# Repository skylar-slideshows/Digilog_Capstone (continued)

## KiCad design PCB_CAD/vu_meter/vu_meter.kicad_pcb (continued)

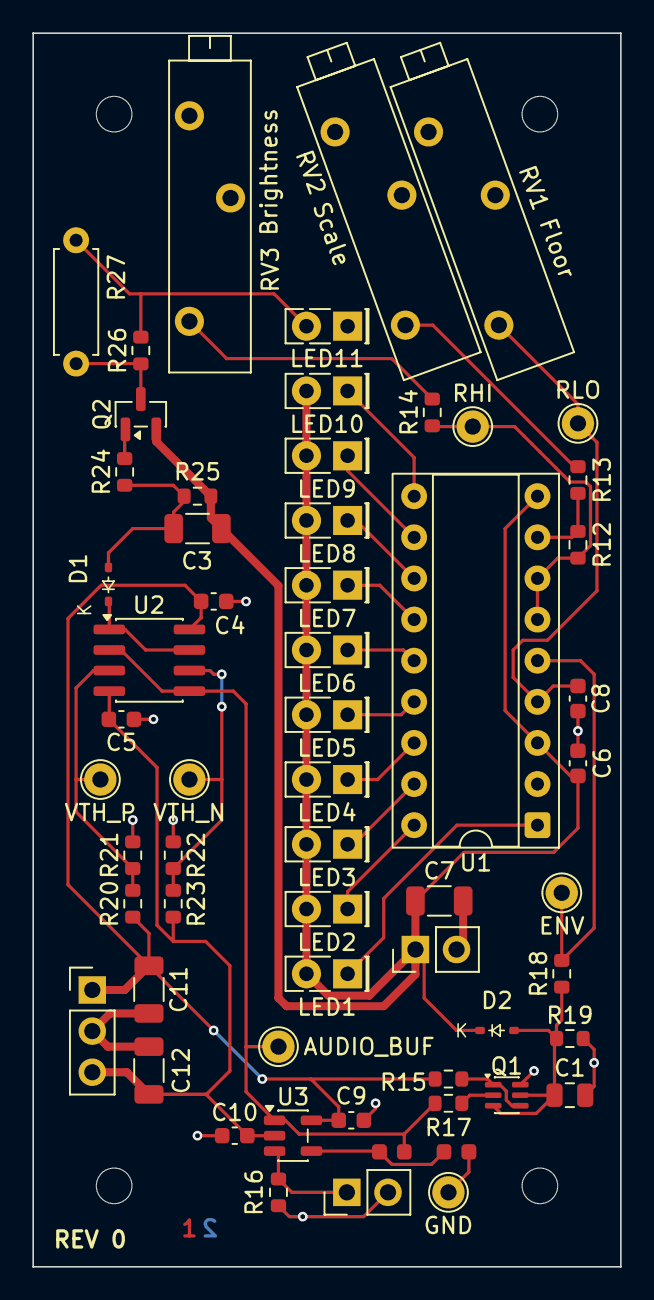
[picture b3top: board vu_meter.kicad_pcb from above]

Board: 2 copper layers, 36.3 x 76.2 mm, 64 parts (0 on the bottom side), 33 nets.

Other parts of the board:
H1, H2, H3, H4: MountingHole_2.2mm_M2

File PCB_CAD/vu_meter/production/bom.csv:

Designator,Footprint,Quantity,Value,LCSC Part #
C1,0805,1,1u,C28323
"C10, C4, C5, C6, C8, C9",0603,6,100n,C1591
"C11, C12, C7",1206,3,10u,C13585
C3,1206,1,2.2u,C50254
D1,D_SOD-323,1,1N4148,C2128
D2,D_SOD-323,1,1N4148WS,C2128
J1,PinHeader_1x03_P2.54mm_Vertical,1,+15 / GND / -15,DNP
J2,PinHeader_1x02_P2.54mm_Vertical,1,+5 / GND,DNP
J3,PinHeader_1x02_P2.54mm_Vertical,1,AUDIO_IN / GND,DNP
"LED1, LED2, LED3, LED4, LED5, LED6, LED7",LED_Rectangular_W5.0mm_H2.0mm,7,LED green,DNP
"LED10, LED8, LED9",LED_Rectangular_W5.0mm_H2.0mm,3,LED yellow,DNP
LED11,LED_Rectangular_W5.0mm_H2.0mm,1,PEAK red,DNP
Q1,SOT-363_SC-70-6,1,MMDT3906,C508227
Q2,SOT-23,1,MMBT3906,C82762
R12,0603,1,3.6k,C22980
R13,0603,1,2.2k,C4190
R14,0603,1,1.5k,C22843
R15,0603,1,15k,C22809
"R16, R25",0603,2,100k,C25803
R17,0603,1,1k,C21190
"R18, R28, R29",0603,3,10k,C25804
R19,0603,1,680k,C25822
"R20, R23",0603,2,330k,C23137
"R21, R22",0603,2,220k,C22961
R24,0603,1,150k,C22807
R26,0603,1,330,C23138
"RV1, RV2",Potentiometer_Bourns_3006P_Horizontal,2,2k,DNP
RV3,Potentiometer_Bourns_3006P_Horizontal,1,10k,DNP
U1,DIP-18_W7.62mm_Socket,1,LM3916,DNP
U2,SOIC-8_3.9x4.9mm_P1.27mm,1,LM393B,C2865059
U3,SOT-23-5,1,TL071H,C4370629

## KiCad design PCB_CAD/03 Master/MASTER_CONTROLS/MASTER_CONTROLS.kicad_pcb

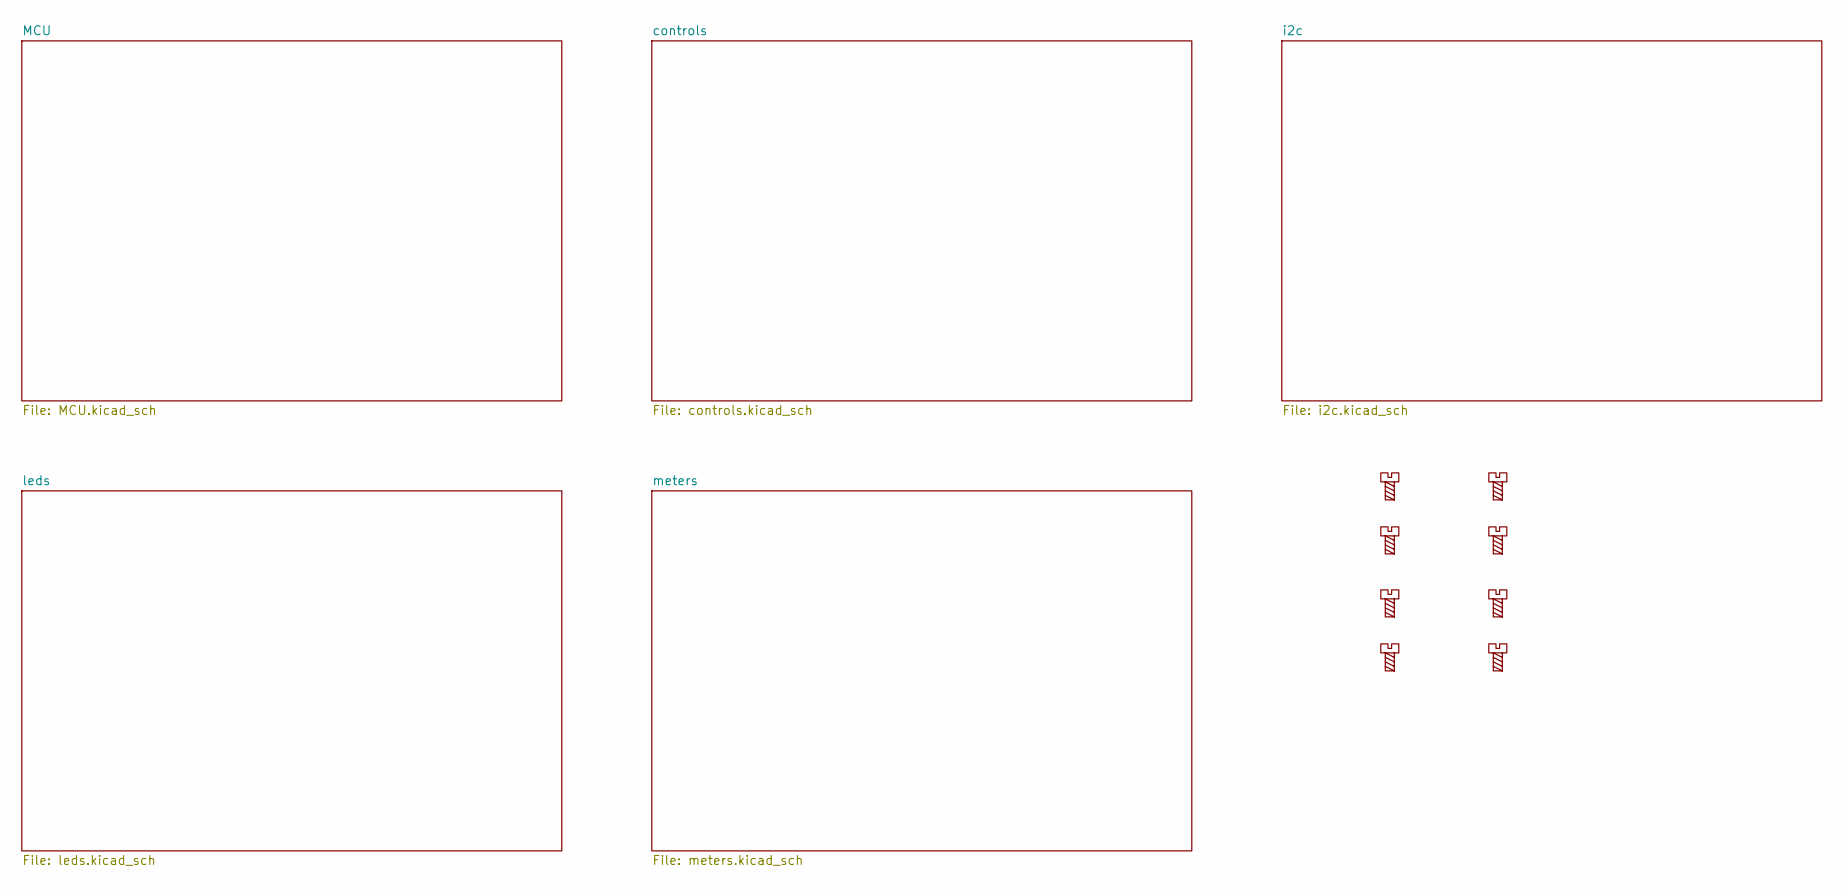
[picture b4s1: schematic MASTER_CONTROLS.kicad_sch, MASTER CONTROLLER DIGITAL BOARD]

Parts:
H1, H2, H3, H4, H5, H6, H7, H8: MountingScrew; MountingHole_3.2mm_M3; LCSC dnp

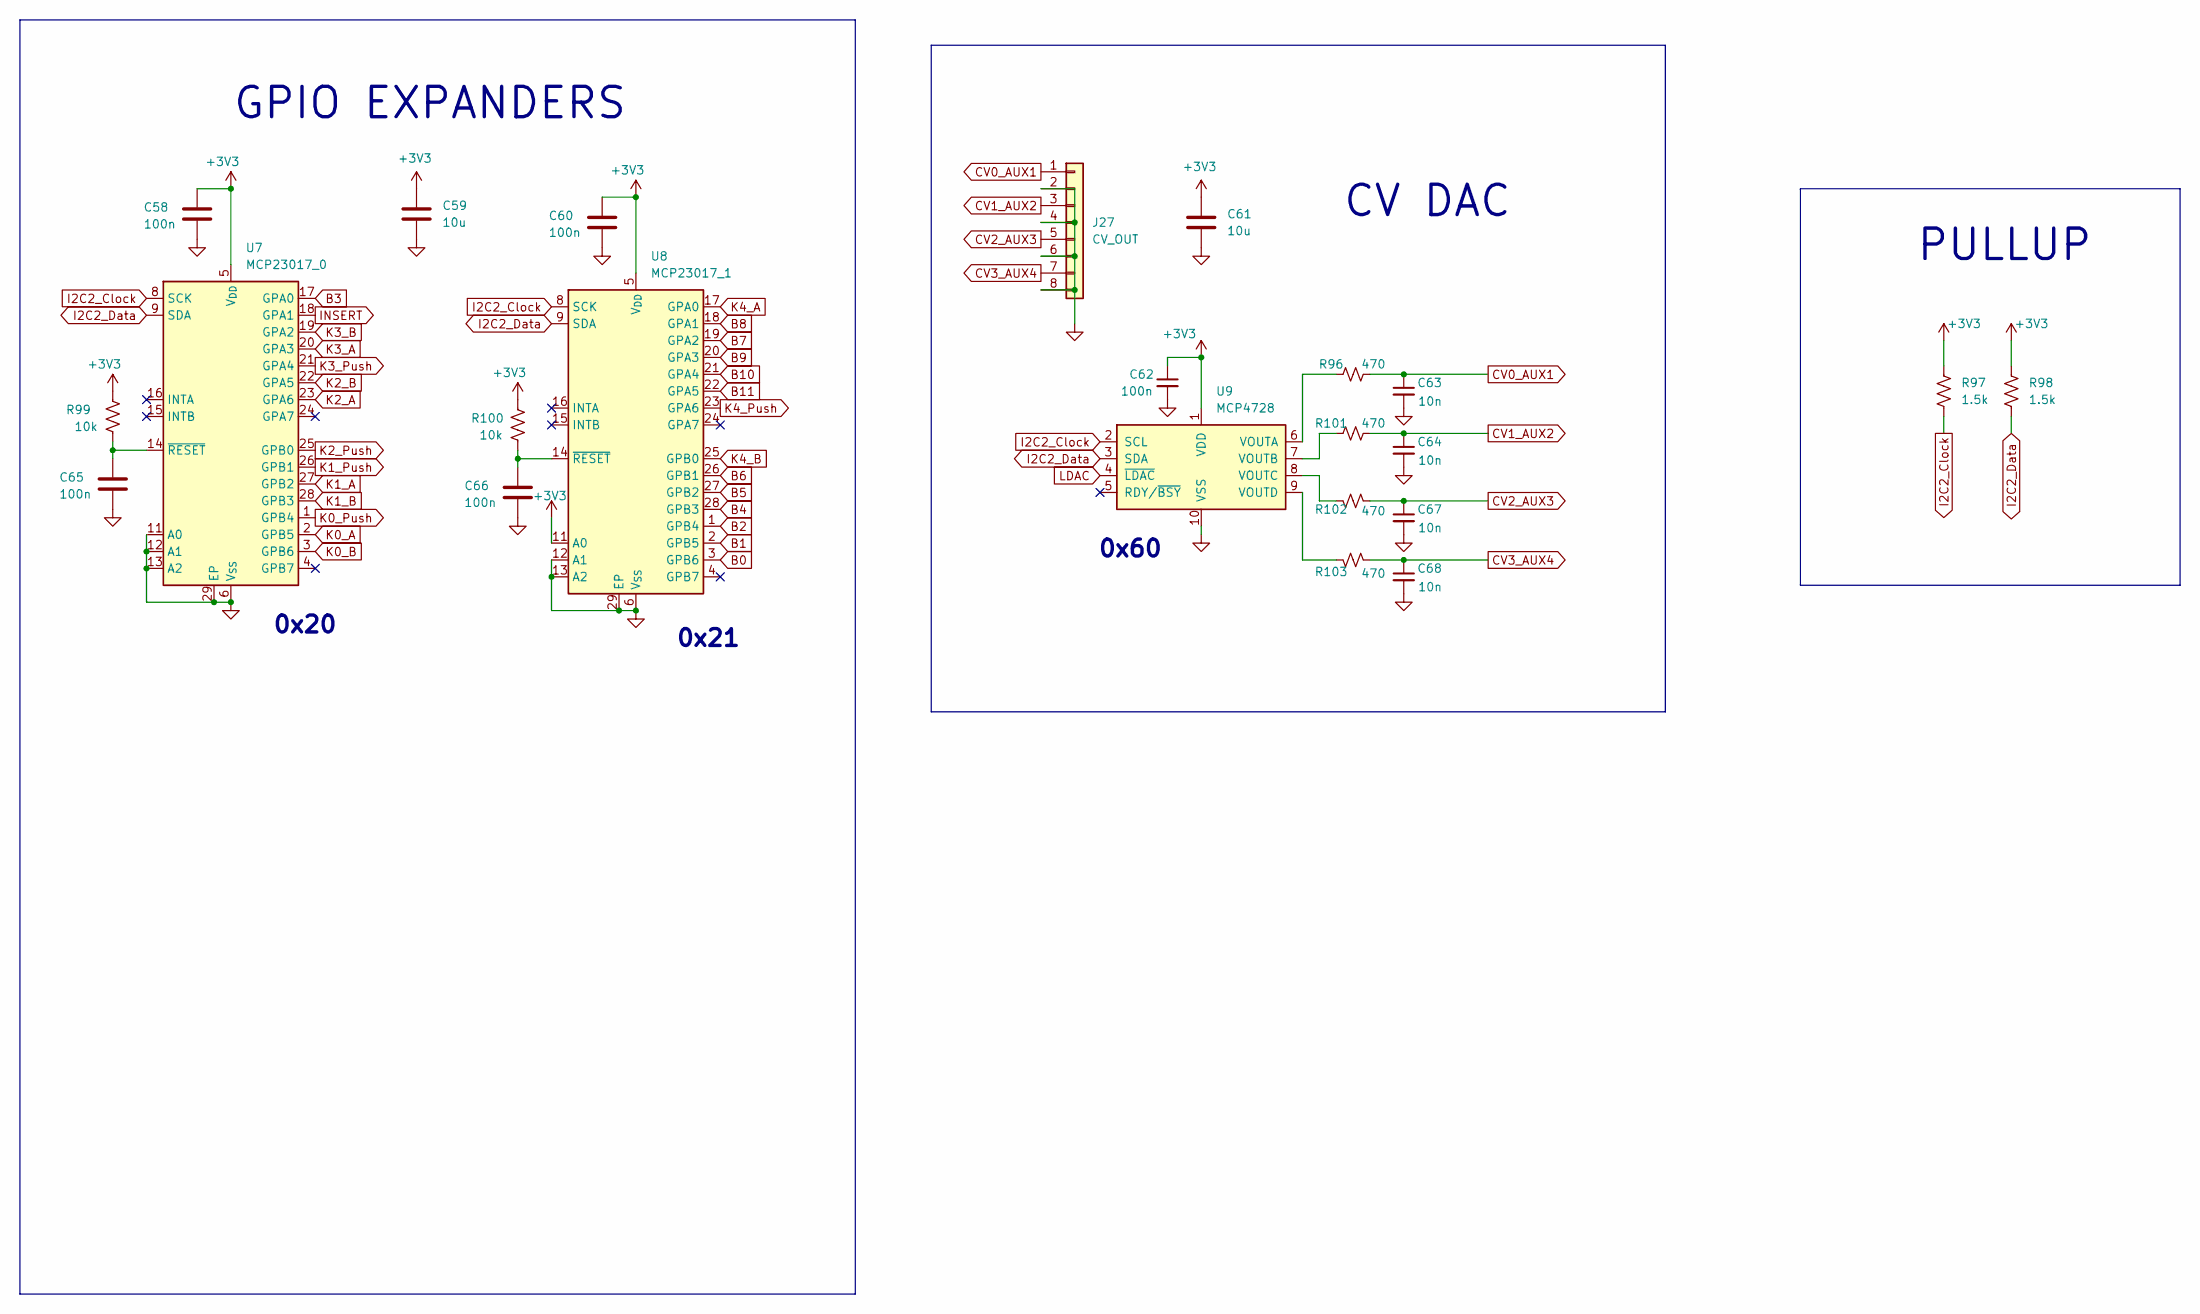
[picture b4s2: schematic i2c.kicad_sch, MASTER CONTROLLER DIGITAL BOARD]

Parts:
C58, C60, C62, C65, C66: 100n; C_0603_1608Metric; LCSC C1590
C59, C61: 10u; C_1206_3216Metric; LCSC C1849
C63, C64, C67, C68: 10n; C_0402_1005Metric; LCSC C1524
J27: CV_OUT; PinHeader_1x08_P2.54mm_Vertical; LCSC DNP
R96, R101, R102, R103: 470; R_0603_1608Metric; LCSC C23179
R97, R98: 1.5k; R_0603_1608Metric; LCSC C22843
R99, R100: 10k; R_0603_1608Metric; LCSC C25804
U7: MCP23017_0; QFN-28-1EP_6x6mm_P0.65mm_EP4.25x4.25mm; LCSC C629439
U8: MCP23017_1; QFN-28-1EP_6x6mm_P0.65mm_EP4.25x4.25mm; LCSC C629439
U9: MCP4728; MSOP-10_3x3mm_P0.5mm; LCSC C108207

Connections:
+3V3: C58.1, C59.1, C60.1, C61.1, C62.1, R97.1, R98.1, R99.1, R100.1, U7.5 (V_{DD}), U8.5 (V_{DD}), U8.11 (A0), U9.1 (VDD); also elsewhere on the board
B0: U8.3 (GPB6); also elsewhere on the board
B1: U8.2 (GPB5); also elsewhere on the board
B2: U8.1 (GPB4); also elsewhere on the board
B3: U7.17 (GPA0); also elsewhere on the board
B4: U8.28 (GPB3); also elsewhere on the board
B5: U8.27 (GPB2); also elsewhere on the board
B6: U8.26 (GPB1); also elsewhere on the board
B7: U8.19 (GPA2); also elsewhere on the board
B8: U8.18 (GPA1); also elsewhere on the board
B9: U8.20 (GPA3); also elsewhere on the board
B10: U8.21 (GPA4); also elsewhere on the board
B11: U8.22 (GPA5); also elsewhere on the board
CV0_AUX1: C63.1, J27.1, R96.2
CV1_AUX2: C64.1, J27.3, R101.2
CV2_AUX3: C67.1, J27.5, R102.2
CV3_AUX4: C68.1, J27.7, R103.2
GND: C58.2, C59.2, C60.2, C61.2, C62.2, C63.2, C64.2, C65.2, C66.2, C67.2, C68.2, J27.2, J27.4, J27.6, J27.8, U7.6 (V_{SS}), U7.11 (A0), U7.12 (A1), U7.13 (A2), U7.29 (EP), U8.6 (V_{SS}), U8.12 (A1), U8.13 (A2), U8.29 (EP), U9.10 (VSS); also elsewhere on the board
I2C2_Clock: R97.2, U7.8 (SCK), U8.8 (SCK), U9.2 (SCL); also elsewhere on the board
I2C2_Data: R98.2, U7.9 (SDA), U8.9 (SDA), U9.3 (SDA); also elsewhere on the board
INSERT: U7.18 (GPA1); also elsewhere on the board
K0_A: U7.2 (GPB5); also elsewhere on the board
K0_B: U7.3 (GPB6); also elsewhere on the board
K0_Push: U7.1 (GPB4); also elsewhere on the board
K1_A: U7.27 (GPB2); also elsewhere on the board
K1_B: U7.28 (GPB3); also elsewhere on the board
K1_Push: U7.26 (GPB1); also elsewhere on the board
K2_A: U7.23 (GPA6); also elsewhere on the board
K2_B: U7.22 (GPA5); also elsewhere on the board
K2_Push: U7.25 (GPB0); also elsewhere on the board
K3_A: U7.20 (GPA3); also elsewhere on the board
K3_B: U7.19 (GPA2); also elsewhere on the board
K3_Push: U7.21 (GPA4); also elsewhere on the board
K4_A: U8.17 (GPA0); also elsewhere on the board
K4_B: U8.25 (GPB0); also elsewhere on the board
K4_Push: U8.23 (GPA6); also elsewhere on the board
LDAC: U9.4 (~LDAC); also elsewhere on the board
unnamed: C65.1, R99.2, U7.14 (~RESET)
unnamed: C66.1, R100.2, U8.14 (~RESET)
unnamed: R96.1, U9.6 (VOUTA)
unnamed: R101.1, U9.7 (VOUTB)
unnamed: R102.1, U9.8 (VOUTC)
unnamed: R103.1, U9.9 (VOUTD)

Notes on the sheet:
0x20
CV DAC
GPIO EXPANDERS
0x60
0x21
PULLUP

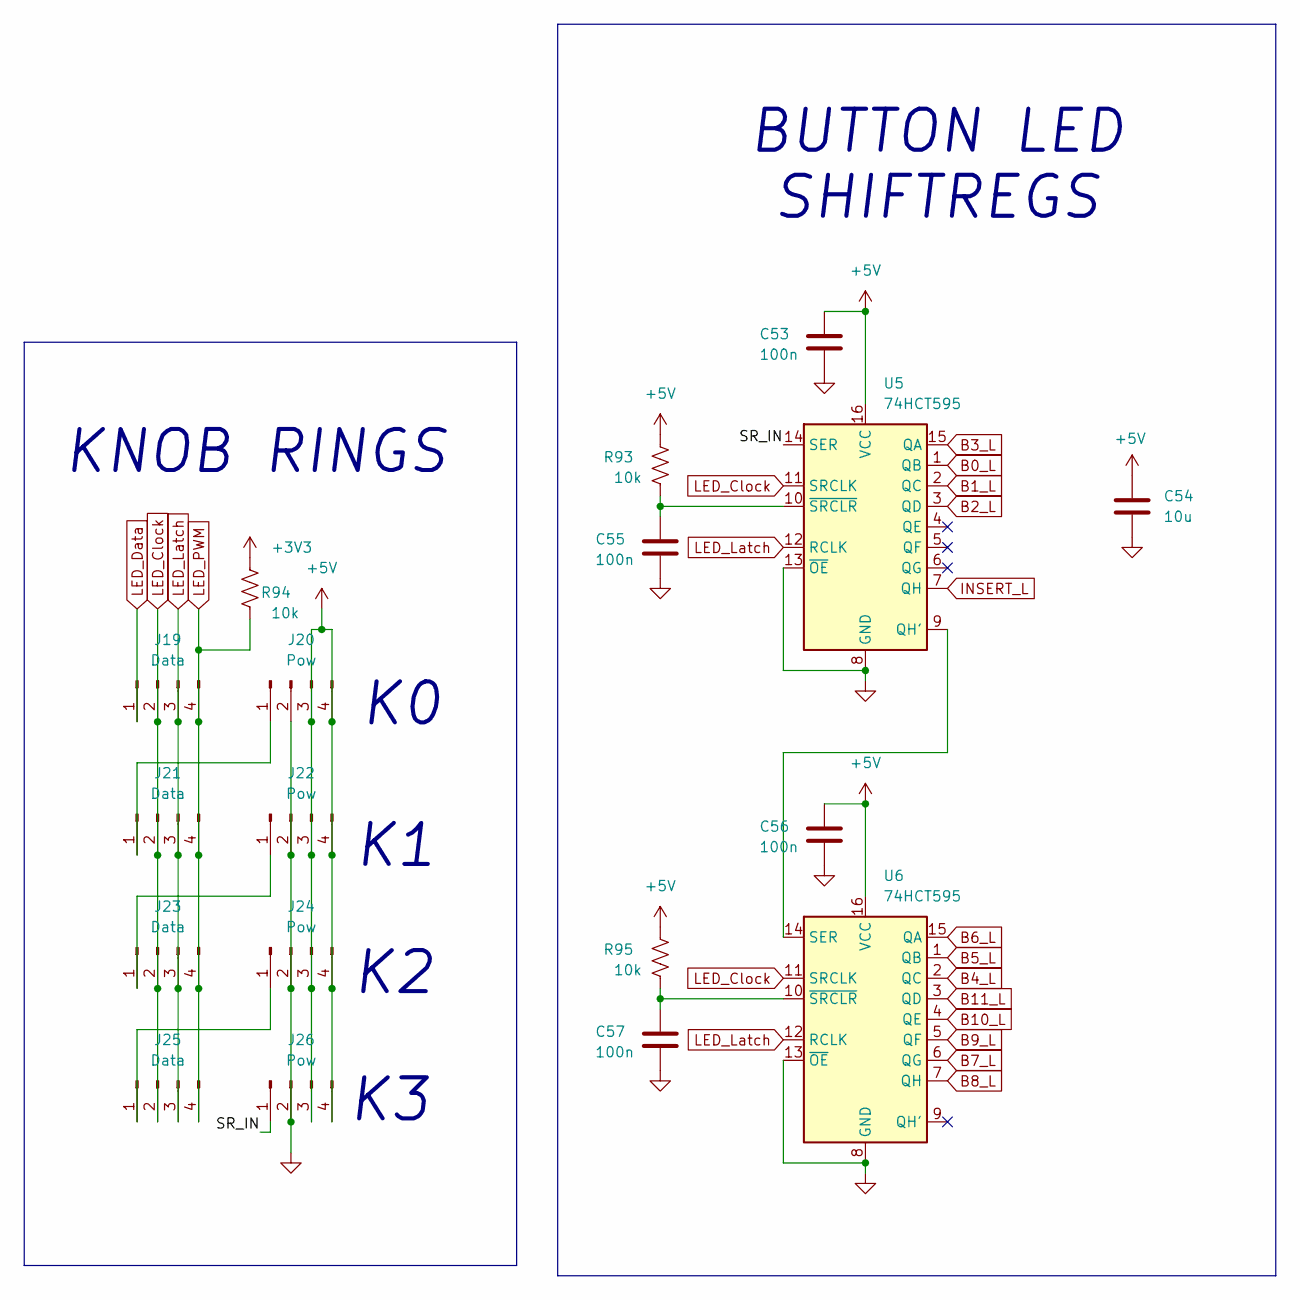
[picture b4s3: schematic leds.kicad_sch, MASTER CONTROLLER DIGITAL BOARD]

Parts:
C53, C55, C56, C57: 100n; C_0603_1608Metric; LCSC C1590
C54: 10u; C_1206_3216Metric; LCSC C1849
J19, J21, J23, J25: Data; PinSocket_1x04_P2.54mm_Vertical; LCSC DNP
J20, J22, J24, J26: Pow; PinSocket_1x04_P2.54mm_Vertical; LCSC DNP
R93, R94, R95: 10k; R_0603_1608Metric; LCSC C25804
U5, U6: 74HCT595; SOIC-16_3.9x9.9mm_P1.27mm; LCSC C282339

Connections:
+3V3: R94.1; also elsewhere on the board
+5V: C53.1, C54.1, C56.1, J20.3, J20.4, J22.3, J22.4, J24.3, J24.4, J26.3, J26.4, R93.1, R95.1, U5.16 (VCC), U6.16 (VCC); also elsewhere on the board
/leds/SR_IN: J26.1, U5.14 (SER)
B0_L: U5.1 (QB); also elsewhere on the board
B1_L: U5.2 (QC); also elsewhere on the board
B2_L: U5.3 (QD); also elsewhere on the board
B3_L: U5.15 (QA); also elsewhere on the board
B4_L: U6.2 (QC); also elsewhere on the board
B5_L: U6.1 (QB); also elsewhere on the board
B6_L: U6.15 (QA); also elsewhere on the board
B7_L: U6.6 (QG); also elsewhere on the board
B8_L: U6.7 (QH); also elsewhere on the board
B9_L: U6.5 (QF); also elsewhere on the board
B10_L: U6.4 (QE); also elsewhere on the board
B11_L: U6.3 (QD); also elsewhere on the board
GND: C53.2, C54.2, C55.2, C56.2, C57.2, J20.2, J22.2, J24.2, J26.2, U5.8 (GND), U5.13 (~OE), U6.8 (GND), U6.13 (~OE); also elsewhere on the board
INSERT_L: U5.7 (QH); also elsewhere on the board
LED_Clock: J19.2, J21.2, J23.2, J25.2, U5.11 (SRCLK), U6.11 (SRCLK); also elsewhere on the board
LED_Data: J19.1; also elsewhere on the board
LED_Latch: J19.3, J21.3, J23.3, J25.3, U5.12 (RCLK), U6.12 (RCLK); also elsewhere on the board
LED_PWM: J19.4, J21.4, J23.4, J25.4, R94.2; also elsewhere on the board
unnamed: J20.1, J21.1
unnamed: J22.1, J23.1
unnamed: J24.1, J25.1
unnamed: U5.9 (QH'), U6.14 (SER)
unnamed: C55.1, R93.2, U5.10 (~SRCLR)
unnamed: C57.1, R95.2, U6.10 (~SRCLR)

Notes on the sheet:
BUTTON LED SHIFTREGS
KNOB RINGS

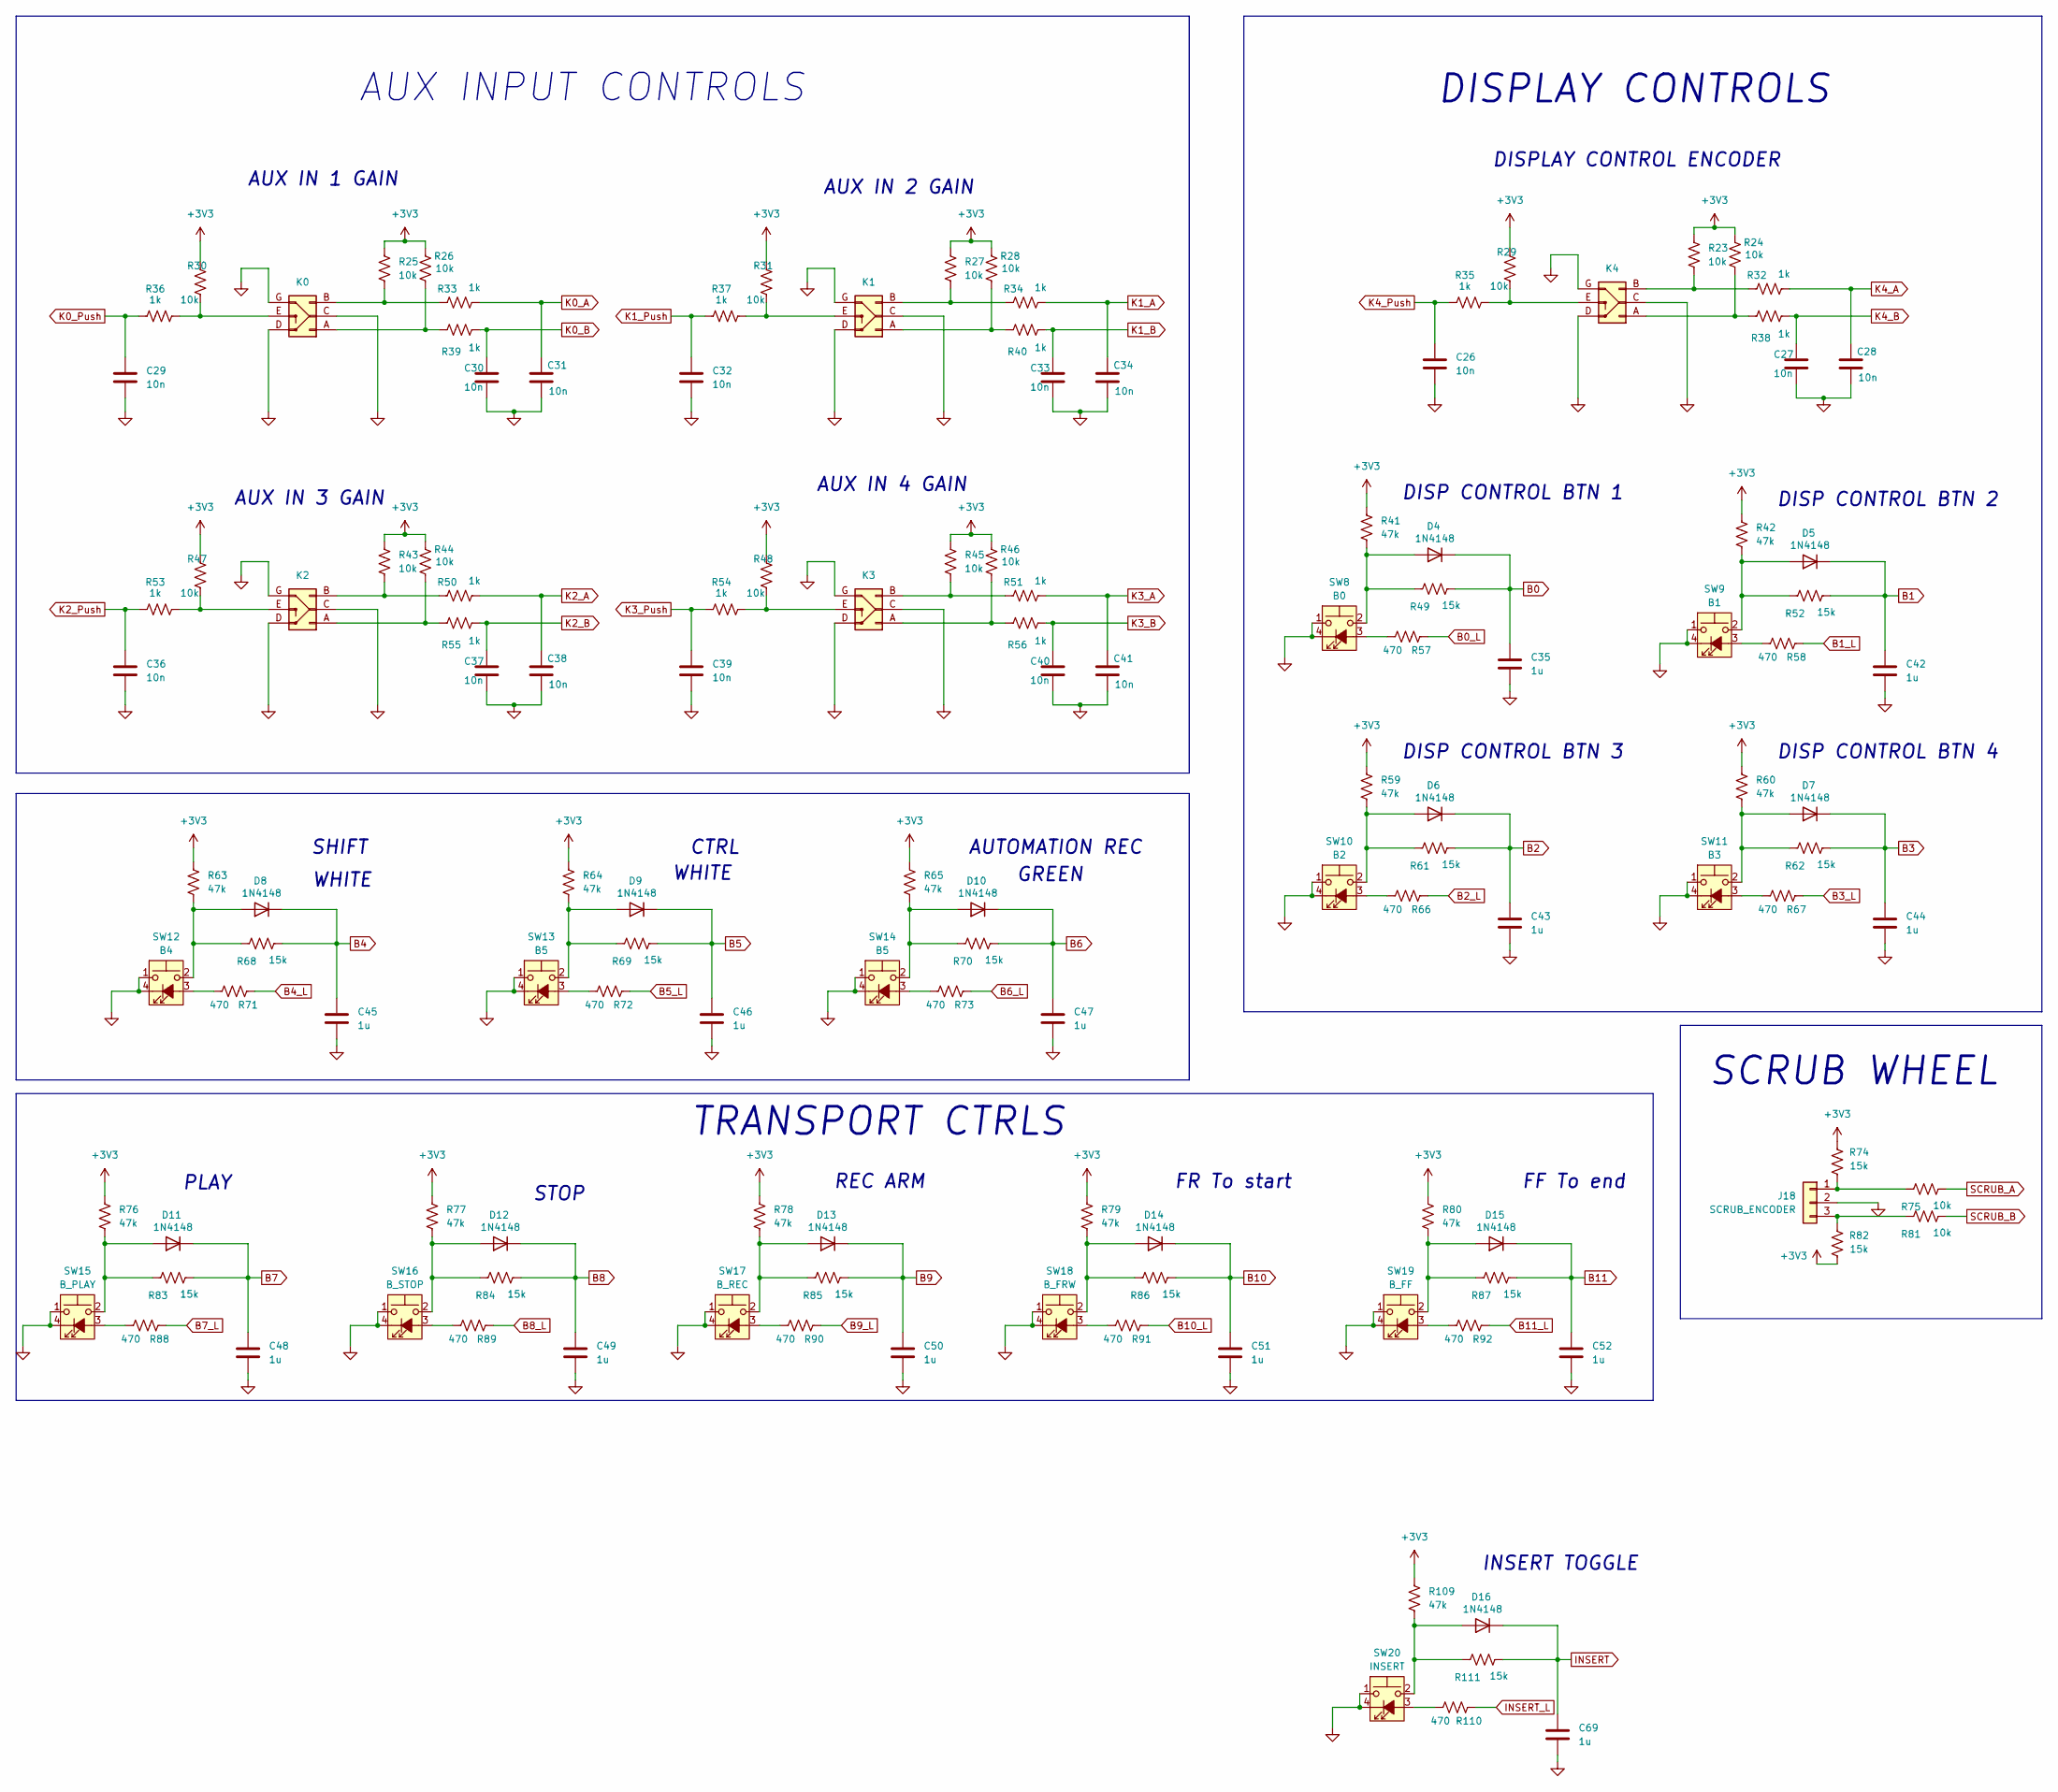
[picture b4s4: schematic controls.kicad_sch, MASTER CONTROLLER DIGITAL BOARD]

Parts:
C26, C27, C28, C29, C30, C31, C32, C33, C34, C36, C37, C38, C39, C40, C41: 10n; C_0402_1005Metric; LCSC C1524
C35, C42, C43, C44, C45, C46, C47, C48, C49, C50, C51, C52, C69: 1u; C_0603_1608Metric; LCSC C15849
D4, D5, D6, D7, D8, D9, D10, D11, D12, D13, D14, D15, D16: 1N4148; D_SOD-323; LCSC C2128
J18: SCRUB_ENCODER; PinHeader_1x03_P2.54mm_Vertical; Part Number 1-0301FBV0T; LCSC DNP
R23, R24, R25, R26, R27, R28, R29, R30, R31, R43, R44, R45, R46, R47, R48, R75, R81: 10k; R_0603_1608Metric; LCSC C25804
R32, R33, R34, R35, R36, R37, R38, R39, R40, R50, R51, R53, R54, R55, R56: 1k; R_0603_1608Metric; LCSC C21190
R41, R42, R59, R60, R63, R64, R65, R76, R77, R78, R79, R80, R109: 47k; R_0603_1608Metric; LCSC C25819
R49, R52, R61, R62, R68, R69, R70, R74, R82, R83, R84, R85, R86, R87, R111: 15k; R_0603_1608Metric; LCSC C22809
R57, R58, R66, R67, R71, R72, R73, R88, R89, R90, R91, R92, R110: 470; R_0603_1608Metric; LCSC C25241
SW3: K4; EC11J0924411; LCSC DNP
SW4: K0; EC11J0924411; LCSC DNP
SW5: K1; EC11J0924411; LCSC DNP
SW6: K2; EC11J0924411; LCSC DNP
SW7: K3; EC11J0924411; LCSC DNP
SW8: B0; CFPB-1CC-4W6_LOWPROF; LCSC DNP
SW9: B1; CFPB-1CC-4W6_LOWPROF; LCSC DNP
SW10: B2; CFPB-1CC-4W6_LOWPROF; LCSC DNP
SW11: B3; CFPB-1CC-4W6_LOWPROF; LCSC DNP
SW12: B4; CFPB-1CC-4W6_LOWPROF; LCSC DNP
SW13, SW14: B5; CFPB-1CC-4W6_LOWPROF; LCSC DNP
SW15: B_PLAY; CFPB-1CC-4W2; LCSC DNP
SW16: B_STOP; CFPB-1CC-4W2; LCSC DNP
SW17: B_REC; CFPB-1CC-4W2; LCSC DNP
SW18: B_FRW; CFPB-1CC-4W2; LCSC DNP
SW19: B_FF; CFPB-1CC-4W2; LCSC DNP
SW20: INSERT; CFPB-1CC-4W6_LOWPROF; LCSC DNP

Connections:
+3V3: R23.1, R24.1, R25.1, R26.1, R27.1, R28.1, R29.1, R30.1, R31.1, R41.1, R42.1, R43.1, R44.1, R45.1, R46.1, R47.1, R48.1, R59.1, R60.1, R63.1, R64.1, R65.1, R74.2, R76.1, R77.1, R78.1, R79.1, R80.1, R82.1, R109.1; also elsewhere on the board
B0: C35.1, D4.1 (K), R49.2; also elsewhere on the board
B0_L: R57.2; also elsewhere on the board
B1: C42.1, D5.1 (K), R52.2; also elsewhere on the board
B1_L: R58.2; also elsewhere on the board
B2: C43.1, D6.1 (K), R61.2; also elsewhere on the board
B2_L: R66.2; also elsewhere on the board
B3: C44.1, D7.1 (K), R62.2; also elsewhere on the board
B3_L: R67.2; also elsewhere on the board
B4: C45.1, D8.1 (K), R68.2; also elsewhere on the board
B4_L: R71.2; also elsewhere on the board
B5: C46.1, D9.1 (K), R69.2; also elsewhere on the board
B5_L: R72.2; also elsewhere on the board
B6: C47.1, D10.1 (K), R70.2; also elsewhere on the board
B6_L: R73.2; also elsewhere on the board
B7: C48.1, D11.1 (K), R83.2; also elsewhere on the board
B7_L: R88.2; also elsewhere on the board
B8: C49.1, D12.1 (K), R84.2; also elsewhere on the board
B8_L: R89.2; also elsewhere on the board
B9: C50.1, D13.1 (K), R85.2; also elsewhere on the board
B9_L: R90.2; also elsewhere on the board
B10: C51.1, D14.1 (K), R86.2; also elsewhere on the board
B10_L: R91.2; also elsewhere on the board
B11: C52.1, D15.1 (K), R87.2; also elsewhere on the board
B11_L: R92.2; also elsewhere on the board
GND: C26.2, C27.2, C28.2, C29.2, C30.2, C31.2, C32.2, C33.2, C34.2, C35.2, C36.2, C37.2, C38.2, C39.2, C40.2, C41.2, C42.2, C43.2, C44.2, C45.2, C46.2, C47.2, C48.2, C49.2, C50.2, C51.2, C52.2, C69.2, J18.2, SW3.C (Pin_2), SW3.D (Pin_4), SW3.G (Pin_6), SW4.C (Pin_2), SW4.D (Pin_4), SW4.G (Pin_6), SW5.C (Pin_2), SW5.D (Pin_4), SW5.G (Pin_6), SW6.C (Pin_2), SW6.D (Pin_4), SW6.G (Pin_6), SW7.C (Pin_2), SW7.D (Pin_4), SW7.G (Pin_6), SW8.1, SW8.4 (K), SW9.1, SW9.4 (K), SW10.1, SW10.4 (K), SW11.1, SW11.4 (K), SW12.1, SW12.4 (K), SW13.1, SW13.4 (K), SW14.1, SW14.4 (K), SW15.1, SW15.4 (K), SW16.1, SW16.4 (K), SW17.1, SW17.4 (K), SW18.1, SW18.4 (K), SW19.1, SW19.4 (K), SW20.1, SW20.4 (K); also elsewhere on the board
INSERT: C69.1, D16.1 (K), R111.2; also elsewhere on the board
INSERT_L: R110.2; also elsewhere on the board
K0_A: C31.1, R33.2; also elsewhere on the board
K0_B: C30.1, R39.2; also elsewhere on the board
K0_Push: C29.1, R36.1; also elsewhere on the board
K1_A: C34.1, R34.2; also elsewhere on the board
K1_B: C33.1, R40.2; also elsewhere on the board
K1_Push: C32.1, R37.1; also elsewhere on the board
K2_A: C38.1, R50.2; also elsewhere on the board
K2_B: C37.1, R55.2; also elsewhere on the board
K2_Push: C36.1, R53.1; also elsewhere on the board
K3_A: C41.1, R51.2; also elsewhere on the board
K3_B: C40.1, R56.2; also elsewhere on the board
K3_Push: C39.1, R54.1; also elsewhere on the board
K4_A: C28.1, R32.2; also elsewhere on the board
K4_B: C27.1, R38.2; also elsewhere on the board
K4_Push: C26.1, R35.1; also elsewhere on the board
unnamed: D4.2 (A), R41.2, R49.1, SW8.2
unnamed: D5.2 (A), R42.2, R52.1, SW9.2
unnamed: D6.2 (A), R59.2, R61.1, SW10.2
unnamed: D7.2 (A), R60.2, R62.1, SW11.2
unnamed: D8.2 (A), R63.2, R68.1, SW12.2
unnamed: D9.2 (A), R64.2, R69.1, SW13.2
unnamed: D10.2 (A), R65.2, R70.1, SW14.2
unnamed: D11.2 (A), R76.2, R83.1, SW15.2
unnamed: D12.2 (A), R77.2, R84.1, SW16.2
unnamed: D13.2 (A), R78.2, R85.1, SW17.2
unnamed: D14.2 (A), R79.2, R86.1, SW18.2
unnamed: D15.2 (A), R80.2, R87.1, SW19.2
unnamed: D16.2 (A), R109.2, R111.1, SW20.2
unnamed: J18.1, R74.1, R75.1
unnamed: J18.3, R81.1, R82.2
unnamed: R24.2, R38.1, SW3.A (Pin_1)
unnamed: R23.2, R32.1, SW3.B (Pin_3)
unnamed: R29.2, R35.2, SW3.E (Pin_5)
unnamed: R26.2, R39.1, SW4.A (Pin_1)
unnamed: R25.2, R33.1, SW4.B (Pin_3)
unnamed: R30.2, R36.2, SW4.E (Pin_5)
unnamed: R28.2, R40.1, SW5.A (Pin_1)
unnamed: R27.2, R34.1, SW5.B (Pin_3)
unnamed: R31.2, R37.2, SW5.E (Pin_5)
unnamed: R44.2, R55.1, SW6.A (Pin_1)
unnamed: R43.2, R50.1, SW6.B (Pin_3)
unnamed: R47.2, R53.2, SW6.E (Pin_5)
unnamed: R46.2, R56.1, SW7.A (Pin_1)
unnamed: R45.2, R51.1, SW7.B (Pin_3)
unnamed: R48.2, R54.2, SW7.E (Pin_5)
unnamed: R57.1, SW8.3 (A)
unnamed: R58.1, SW9.3 (A)
unnamed: R66.1, SW10.3 (A)
unnamed: R67.1, SW11.3 (A)
unnamed: R71.1, SW12.3 (A)
unnamed: R72.1, SW13.3 (A)
unnamed: R73.1, SW14.3 (A)
unnamed: R88.1, SW15.3 (A)
unnamed: R89.1, SW16.3 (A)
unnamed: R90.1, SW17.3 (A)
unnamed: R91.1, SW18.3 (A)
unnamed: R92.1, SW19.3 (A)
unnamed: R110.1, SW20.3 (A)
SCRUB_A: R75.2; also elsewhere on the board
SCRUB_B: R81.2; also elsewhere on the board

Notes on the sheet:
DISP CONTROL BTN 4
WHITE
AUTOMATION REC
AUX IN 4 GAIN
STOP
TRANSPORT CTRLS
AUX IN 2 GAIN
SCRUB WHEEL
CTRL
FR To start
SHIFT
DISP CONTROL BTN 2
REC ARM
AUX INPUT CONTROLS
INSERT TOGGLE
GREEN
DISP CONTROL BTN 3
PLAY
AUX IN 3 GAIN
AUX IN 1 GAIN
DISPLAY CONTROLS
DISPLAY CONTROL ENCODER
DISP CONTROL BTN 1
FF To end
